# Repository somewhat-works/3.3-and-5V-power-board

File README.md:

# 3.3-and-5V-power-board
Its a powerboard it makes 3.3V and 5V for powering EVMs and sensors.
12V input.
Location for arduino nano for optional display out using ADC.

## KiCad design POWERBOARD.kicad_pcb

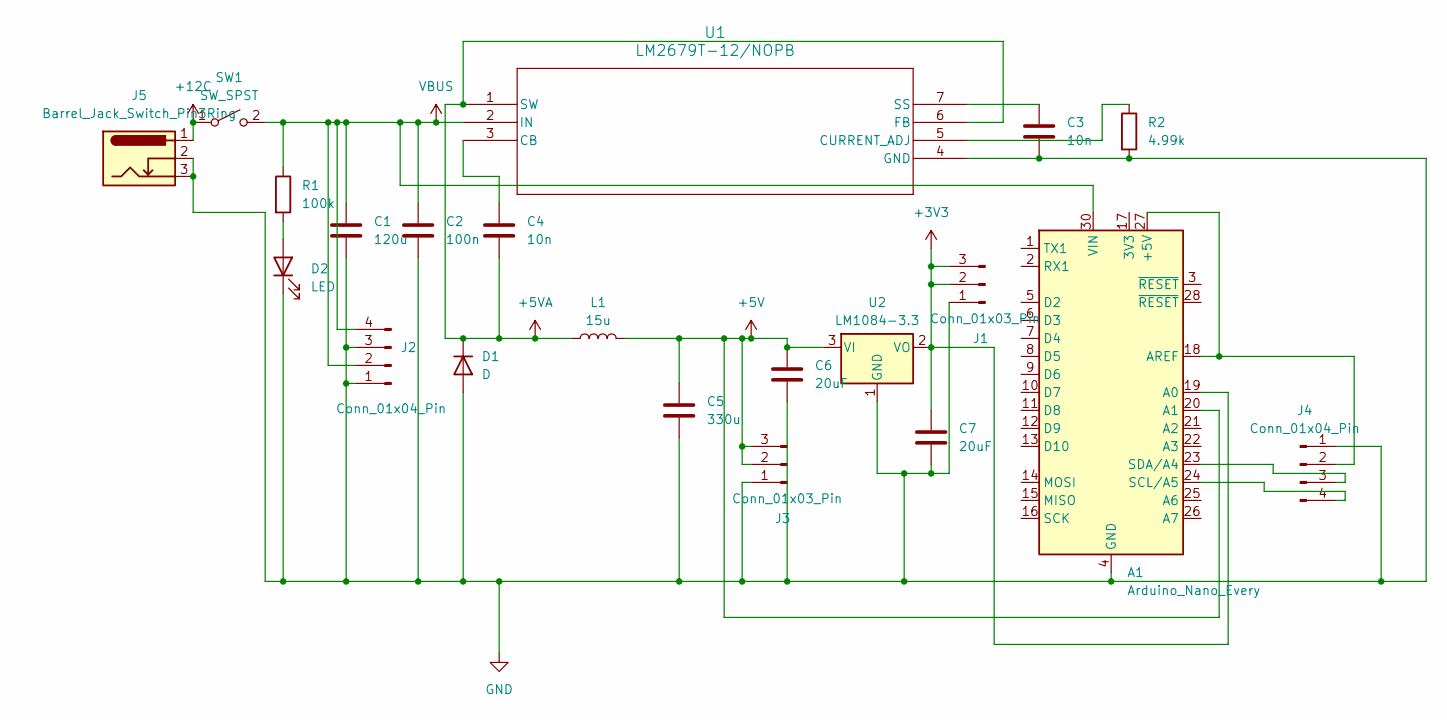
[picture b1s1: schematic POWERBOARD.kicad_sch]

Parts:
A1: Arduino_Nano_Every; Arduino_Nano
C1: 120u; CP_Radial_D10.0mm_P5.00mm
C2: 100n; C_Disc_D7.5mm_W4.4mm_P5.00mm
C3, C4: 10n; C_Disc_D6.0mm_W4.4mm_P5.00mm
C5: 330u; CP_Radial_D8.0mm_P3.50mm
C6, C7: 20uF; C_Disc_D6.0mm_W4.4mm_P5.00mm
D1: D; TO533P482X997X1956-2P
D2: LED; LED_D5.0mm_Clear
J1, J3: Conn_01x03_Pin; 1548129
J2, J4: Conn_01x04_Pin; PinHeader_1x04_P1.27mm_Vertical
J5: Barrel_Jack_Switch_Pin3Ring; 694106301002_1
L1: 15u; 2303VRC
R1: 100k; R_Axial_DIN0207_L6.3mm_D2.5mm_P7.62mm_Horizontal
R2: 4.99k; R_Axial_DIN0207_L6.3mm_D2.5mm_P7.62mm_Horizontal
SW1: SW_SPST
U1: LM2679T-12/NOPB; TA07B
U2: LM1084-3.3; T03B

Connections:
+3V3: A1.19 (A0), C7.1, J1.2, J1.3, U2.2 (VO)
+5V: A1.20 (A1), C5.1, C6.1, J3.2, J3.3, L1.2, U2.3 (VI)
+5VA: C4.2, D1.1 (K), L1.1, U1.1 (SW), U1.6 (FB)
+12C: J5.1, SW1.1 (A)
GND: A1.4 (GND), A1.29 (GND), C1.2, C2.2, C3.2, C5.2, C6.2, C7.2, D1.2 (A), D2.1 (K), J1.1, J2.1, J2.3, J3.1, J4.1, J5.2, J5.3, R2.2, U1.4 (GND), U2.1 (GND)
unnamed: A1.18 (AREF), A1.27 (+5V), J4.2
unnamed: A1.24 (SCL/A5), J4.4
unnamed: A1.23 (SDA/A4), J4.3
unnamed: D2.2 (A), R1.2
unnamed: C4.1, U1.3 (CB)
unnamed: R2.1, U1.5 (CURRENT_ADJ)
unnamed: C3.1, U1.7 (SS)
VBUS: A1.30 (VIN), C1.1, C2.1, J2.2, J2.4, R1.1, SW1.2 (B), U1.2 (IN)

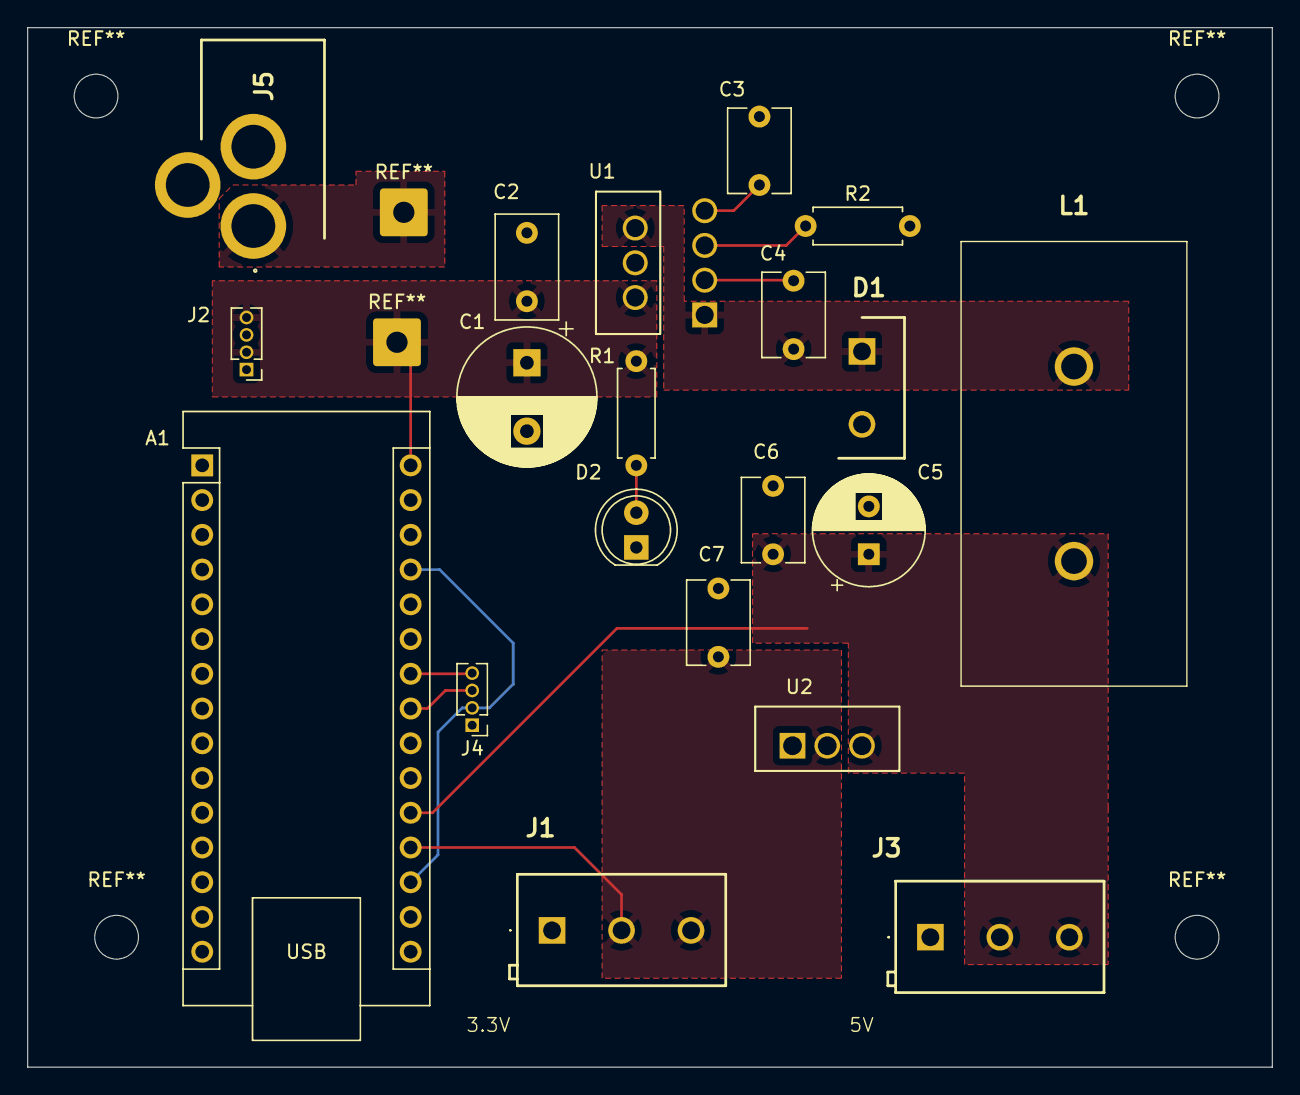
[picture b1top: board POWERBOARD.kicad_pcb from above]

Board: 2 copper layers, 91.0 x 76.0 mm, 20 parts (0 on the bottom side), 12 nets.

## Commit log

2025-01-29 Add files via upload
    the electronics
2025-01-30 Add files via upload
    mouser part numbers and costs
